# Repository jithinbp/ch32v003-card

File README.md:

# CH32V003 based Wedding Invites

Schematics originally based on [Christmas LED ball](https://www.hackster.io/fabiosouza/christmas-ornament-based-on-ch32v003-riscv-mcu-2793db) .

## Features

+ USB C 6 pin connector with TP4057 for charging
+ 3.7V battery
+ CH32V003 processor
+ 14 LEDs
+ 1 RGB LED
+ IR Receiver
+ Reed switch for timing the POV display
+ footprints for BMP280 ( not tested yet )

## Software features

+ RGB LED control
+ PWM fading of LEDs
+ IR receiver via interrupt
+ Interrupt wake up and deep sleep
+ Persistence of vision display using 8 LEDs

## Author links

+ [Jithin BP](https://github.com/jithinbp/)
+ [CSpark Research](https://github.com/csparkresearch/)

## Credits

+ [Fábio Souza](https://github.com/FBSeletronica) for the CH32v003 layout for the LED christmas ball which served as a starting point for this work.
+ [CNLohr] (https://github.com/cnlohr/) for the many examples on [ch32v003fun](https://github.com/cnlohr/ch32v003fun) from where I lifted sections for H/W interrupts (for IR) , deep sleep mode and wakeup , and PWM . The datasheet was also of much help. :)

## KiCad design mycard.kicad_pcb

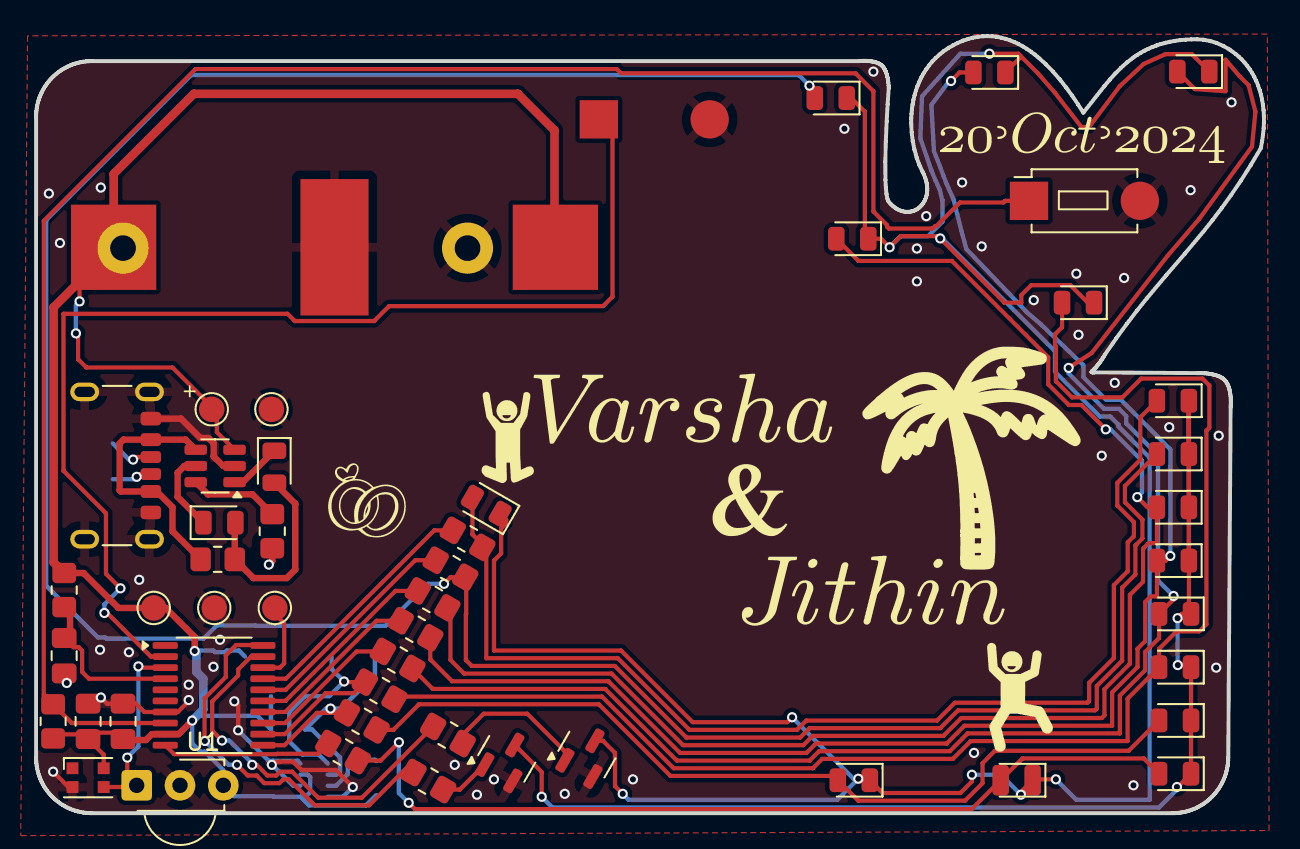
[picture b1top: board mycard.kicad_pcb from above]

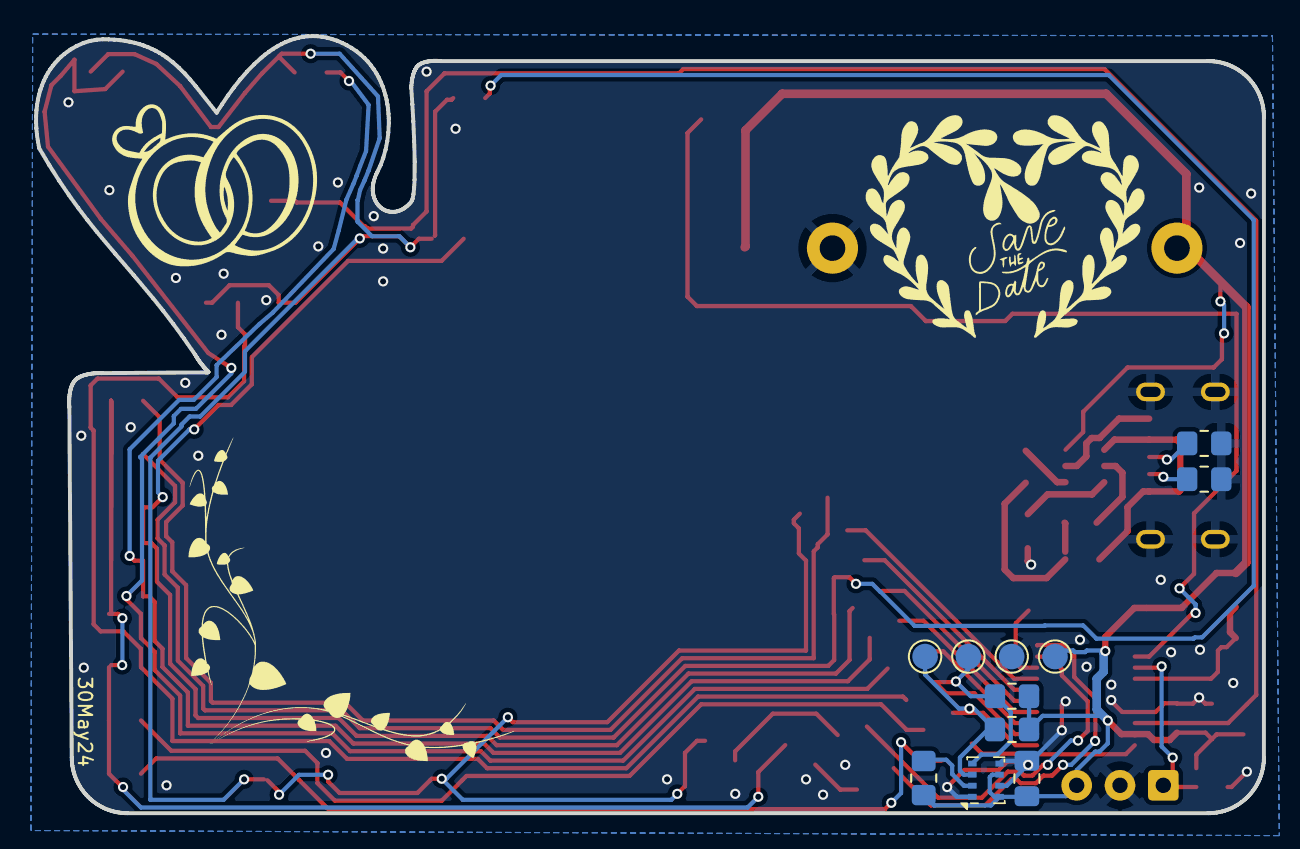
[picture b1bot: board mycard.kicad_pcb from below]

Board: 2 copper layers, 72.0 x 45.6 mm, 62 parts (11 on the bottom side), 37 nets.

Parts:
BT1: BC-2001; BatteryHolder_Multicomp_BC-2001_1x2032
BT2: CR2032; BatteryHolder_Keystone_3002_1x2032
C1, C3, C5: 100nF; C_0805_2012Metric_Pad1.18x1.45mm_HandSolder
C2: 10uF; C_0805_2012Metric_Pad1.18x1.45mm_HandSolder
D1, D4, D7, D10, D13: D-B080508B1-KS2; LED_0805_2012Metric
D2, D5, D8, D11, D14, D17, D18: e17-21SURC/S530-A3/TR8; LED_0805_2012Metric
D3, D6, D9, D12, D15, D16: NCD0805G1; LED_0805_2012Metric
D19: WS2812B-2020; LED_WS2812B-2020_PLCC4_2.0x2.0mm
J1, J2, J3, J4, J5: Conn_01x01_Pin; TestPoint_Pad_D1.5mm
P1: USB_C_Plug_USB2.0_6pin; USB_C_Receptacle_GCT_USB4125-xx-x_6P_TopMnt_Horizontal
Q1, Q2: BC817; SOT-23
R1, R12, R13, R14, R15, R16, R17: 10K; R_0805_2012Metric_Pad1.20x1.40mm_HandSolder
R2, R3, R4, R5, R6, R7, R8, R9, R10, R11: 1K; R_0805_2012Metric_Pad1.20x1.40mm_HandSolder
R18, R19: 5.1K; R_0805_2012Metric_Pad1.20x1.40mm_HandSolder
SW1: SW_Reed; SW_PUSH_1P1T_6x3.5mm_H4.3_APEM_MJTP1243
SW2: SW_Push; SW_PUSH_1P1T_6x3.5mm_H4.3_APEM_MJTP1243
U1: CH32V003F4P6; TSSOP-20_4.4x6.5mm_P0.65mm
U2: TSOP382xx; Vishay_MINICAST-3Pin
U3: BMP280; Bosch_LGA-8_2x2.5mm_P0.65mm_ClockwisePinNumbering
U5: TP4057; SOT-23-6
tp3v3: Conn_01x01_Pin; TestPoint_Pad_D1.5mm
tpgnd1: Conn_01x01_Pin; TestPoint_Pad_D1.5mm
tpscl1: Conn_01x01_Pin; TestPoint_Pad_D1.5mm
tpsda1: Conn_01x01_Pin; TestPoint_Pad_D1.5mm

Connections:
+3V3: BT1.1 (+), BT2.1 (+), C2.1, C3.2, C5.1, D19.4 (VDD), J1.1, J4.1, R1.1, R12.2, R13.2, R14.2, R15.2, U1.9 (VDD), U2.3 (Vs), U3.6 (VDDIO), U3.8 (VDD), U5.3 (BAT), tp3v3.1
/VUSB: P1.A9 (VBUS), P1.B9 (VBUS), R17.1, U5.4 (VCC)
BT: R15.1, SW2.1, U1.8 (PD0)
C1: R10.1, U1.19 (PD2)
C2: R11.1, U1.20 (PD3)
GND: BT1.2 (-), BT2.2 (-), C1.1, C2.2, C3.1, C5.2, D19.2 (VSS), J2.1, J5.1, P1.A12 (GND), P1.B12 (GND), P1.S1 (SHIELD), Q1.2 (E), Q2.2 (E), R16.2, R18.2, R19.2, SW1.2, SW2.2, U1.7 (VSS), U2.2 (GND), U3.1 (GND), U3.5 (SDO), U3.7 (GND), U5.2 (GND), tpgnd1.1
IR: D19.3 (DIN), U1.3 (PD6), U2.1 (OUT)
L1: D1.2 (A), D9.2 (A), R2.2
L2: D2.2 (A), D10.2 (A), R3.2
L3: D3.2 (A), D11.2 (A), R4.2
L4: D4.2 (A), D12.2 (A), R5.2
L5: D5.2 (A), D13.2 (A), R6.2
L6: D6.2 (A), D14.2 (A), R7.2
L7: D7.2 (A), D15.2 (A), R8.2
L8: D8.2 (A), D16.2 (A), R9.2
unnamed: D1.1 (K), D2.1 (K), D3.1 (K), D4.1 (K), D5.1 (K), D6.1 (K), D7.1 (K), D8.1 (K), Q1.3 (C)
unnamed: D9.1 (K), D10.1 (K), D11.1 (K), D12.1 (K), D13.1 (K), D14.1 (K), D15.1 (K), D16.1 (K), Q2.3 (C)
unnamed: D17.2 (A), D18.2 (A), R17.2
unnamed: D17.1 (K), U5.1 (CHRG)
unnamed: D18.1 (K), U5.5 (STDBY)
unnamed: P1.A5 (CC), R18.1
unnamed: P1.B5 (VCONN), R19.1
unnamed: Q1.1 (B), R10.2
unnamed: Q2.1 (B), R11.2
unnamed: C1.2, R1.2, U1.4 (NRST/PD7)
unnamed: R2.1, U1.10 (PC0)
unnamed: R5.1, U1.13 (PC3)
unnamed: R6.1, U1.14 (PC4)
unnamed: R7.1, U1.15 (PC5)
unnamed: R8.1, U1.16 (PC6)
unnamed: R9.1, U1.17 (PC7)
unnamed: R14.1, U3.2 (CSB)
unnamed: R16.1, U5.6 (PROG)
REED: SW1.1, U1.2 (PD5)
SCL: R4.1, R13.1, U1.12 (PC2), U3.4 (SCK), tpscl1.1
SDA: R3.1, R12.1, U1.11 (PC1), U3.3 (SDI), tpsda1.1
SWIO: J3.1, U1.18 (PD1)

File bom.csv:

Id,Designator,Footprint,Quantity,Designation,Supplier and ref
1,"D16,D11,D14,D15,D13,D10,D12,D8,D9",LED_0805_2012Metric,9,PINK LED,ok
2,"D7,D17,D3,D6",LED_0805_2012Metric,4,RED LED,ok
3,D19,LED_WS2812B-2020_PLCC4_2.0x2.0mm,1,WS2812B-2020,ok
4,U5,SOT-23-6,1,TP4057,ok
5,"R11,R7,R10,R5,R9,R3,R6,R2,R4,R8",R_0805_2012Metric_Pad1.20x1.40mm_HandSolder,10,1K,ok
6,"R16,R15,R17,R1,R14,R12,R13",R_0805_2012Metric_Pad1.20x1.40mm_HandSolder,7,10K,ok
7,C2,C_0805_2012Metric_Pad1.18x1.45mm_HandSolder,1,10uF,ok
8,"Q1,Q2",SOT-23,2,BC817,ok
9,"D5,D4",LED_0805_2012Metric,2,BLUE LED,ok
11,"D2,D18,D1",LED_0805_2012Metric,3,GREEN LED,ok
12,"C1,C3,C5",C_0805_2012Metric_Pad1.18x1.45mm_HandSolder,3,100nF,ok
15,P1,USB_C_Receptacle_GCT_USB4125-xx-x_6P_TopMnt_Horizontal,1,USB_C_Plug_USB2.0_6pin,ok
16,U2,Vishay_MINICAST-3Pin,1,TSOP382xx,0
17,U1,TSSOP-20_4.4x6.5mm_P0.65mm,1,CH32V003F4P6,ok
18,SW2,SW_PUSH_1P1T_6x3.5mm_H4.3_APEM_MJTP1243,1,SW_Push,ok
19,U3,Bosch_LGA-8_2x2.5mm_P0.65mm_ClockwisePinNumbering,1,BMP280,
20,"R19,R18",R_0805_2012Metric_Pad1.20x1.40mm_HandSolder,2,5.1K,

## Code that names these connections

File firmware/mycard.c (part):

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	TIM1->BDTR |= TIM_MOE;
	// Enable TIM1
	TIM1->CTLR1 |= TIM_CEN;
	funPinMode( PD2, GPIO_CFGLR_OUT_10Mhz_AF_PP );	//enable alt func
	GPIOC->BSHR |= 0b11100 ; // set new
	for(int n=0;n<times;n++){
		for(int x=1;x<255;x++){
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	}
	// Stop TIM1
	TIM1->CTLR1 &= ~TIM_CEN;
	funPinMode( PD2, GPIO_CFGLR_OUT_10Mhz_PP );	//back to push pull
}


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	

	// GPIO D3,D4 for input pin change.
	//funPinMode( PD3, GPIO_CFGLR_IN_FLOAT );
	funPinMode( PD4, GPIO_CFGLR_IN_FLOAT );

	funPinMode( PD0,  GPIO_CFGLR_IN_PUPD ); //switch

	funDigitalWrite( PA2, FUN_HIGH );
	funDigitalWrite( PD0, FUN_HIGH );

	//funPinMode( PD6,  GPIO_CFGLR_OUT_10Mhz_PP ); //rgb

	funPinMode( PC0,  GPIO_CFGLR_OUT_10Mhz_PP );
	funPinMode( PC1,  GPIO_CFGLR_OUT_10Mhz_PP );
	funPinMode( PC2,  GPIO_CFGLR_OUT_10Mhz_PP );
	funPinMode( PC3,  GPIO_CFGLR_OUT_10Mhz_PP );
	funPinMode( PC4,  GPIO_CFGLR_OUT_10Mhz_PP );
	funPinMode( PC5,  GPIO_CFGLR_OUT_10Mhz_PP );
	funPinMode( PC6,  GPIO_CFGLR_OUT_10Mhz_PP );
	funPinMode( PC7,  GPIO_CFGLR_OUT_10Mhz_PP );

	// OUTPUT TRANSISTORS
	funPinMode( PD2, GPIO_CFGLR_OUT_10Mhz_PP );	
	funPinMode( PD3, GPIO_CFGLR_OUT_10Mhz_PP );	
	funDigitalWrite( PD2, FUN_LOW );
	funDigitalWrite( PD3, FUN_LOW );



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	PWR->CTLR |= PWR_CTLR_PDDS;


	funPinMode( PD5,  GPIO_CFGLR_IN_PUPD ); //REED switch
	funDigitalWrite(PD5, FUN_HIGH); //pullup reed switch


	enableAutoWakeup();
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
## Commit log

2024-06-18 first commit. KiCAD files and firmware
2024-06-18 edit readme
